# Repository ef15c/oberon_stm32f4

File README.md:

# Oberon STM32F4
Portage of Oberon system to stm32f429i-disco board<br><br>

**Version 15 released!**
## Oberon System
**Improvements:**  

* Divison by zero check is now done by hardware.
* USB Host and Device support added. HID Host and MTP Responder Device are available.
* 16bit integer added to the OM4 compiler (HALFWORD). HALSET and BYTESET types added.
* CLEAR standard procedure is added for setting RECORD and ARRAY variables to zero.
* CPU register protection improved in interrupt handlers.
* Code disassembly tools improved
* The mouse pointer is now managed by hardware. It is no more frozen when system is busy.
* Mira program "chaos esthétique" has been added for testing implementation of REAL type in OM4 compiler.
* Tuning of VESA timings
* Oberon.Batch command has been added for execution of several commands by one mouse click.
* OFS2 replaces the original Project Oberon File System:
  * the sector size is now 2KB instead of 1KB
  * the file size limit is now 12MB instead of 3MB.
  * date and size data are duplicated in the directory entry. Reading the files header sector is no more required in `System.Directory *!` execution.

**Version 14 released!**
## Oberon System
**Improvements:**  

* Edit.ChangeOffset allows formatting indices and exponents in texts  
* Mouse wheel support in text frames
* Scrolling text is now faster
* VGA stability improved
* HOME and END keys supported
* NIL dereferences (trap 4) detection improved
* tests of OM4 compiler with Advent Of Code 2025 puzzles

**Fixes:**

* CapsLock sometimes freezes keyboard fixed
* LED blinking on system panic fixed
* wrong mouse pointer shape in text frames fixed

## MSP430 Oberon compiler
The compiler and linker were rewritten in order to eliminate unused code and data.  
Libraries can now include many procedures and only the ones used in the program
will be placed in the generated firmware.  

A new example including a bootloader and code in RAM feature has been added (bootloader and sDiary).

This toolchain is also available on GNU/Linux amd64 [here](https://github.com/ef15c/omsp).
## Hardware
The base board PCB can be ordered [here](https://www.pcbway.com/project/shareproject/Oberon_STM32F429I_DISCO_station_af64426e.html)  
## Previous releases
A rudimentary image manipulation module is available. It allows to display 8bpp indexed colors BMP and can take screenshots.

**The 12th release contains a major improvement:** the code and strings of the modules can be stored
 in the microcontroller's flash memory and executed in place.
In this case, the global data will be placed is SRAM.  
Previously, the modules had to be loaded into the SDRAM for execution.  
There are a lot of advantages doing this:  

* The code executes 8 times faster, by avoiding the competition between CPU and VGA system for SDRAM access.  
* More SDRAM is available for modules that remain in SDRAM and for the heap.
* If the Oberon system and the compiler are both placed in embedded flash memory,
 the system is guaranteed to boot and compile even if incoherent recompilation has been done on vital modules.
 
 To put modules in embedded flash, follow this procedure:
 
 * Prelink the modules using the command **OM4L.LinkEF**. Example: `OM4L.LinkEF Modules System Edit OM4P ~`  
This will produce a .efb file that will be later placed in the embedded flash memory.
 * Reboot the station in legacy SDRAM mode by pressing the SW1 button on the base board and the reset button on the SMT429I-DISCO board.
  This is mandatory because it is not safe to modify the embedded flash memory while executing it.
 * Install the .efb file using the command **OM4X.LoadEF**. Example: `OM4X.LoadEF OM4P.efb`  
The installation can be verified by comparing the .efb file and the content of the embedded flash,
 using the command **OM4L.CompareEF**. Example: `OM4L.CompareEF OM4P.efb`  
The installation is successful if the output of this command ends with the word "same".
 * Reboot the station without pressing SW1 button. The station should now execute the Oberon system and the compiler from embedded flash.
 This can be checked with the command **System.ShowModules**. In the window that appears,
  all lines refering a module stored in embedded flash will end with the number -1. Example: `OM4P	 0802E7B4 0802F1F4  -1`

Reminder: starting wiht the release 9, it is now easy to launch user actions immediately after system startup.
Put your code in the initialization section of the OnStartup module and compile it.

<br>
QWERTY keyboard can be activated by middle clicking on the text "OM4P.Compile InputQwerty.Mod ~"<br>
displayed in yellow in the middle of the System.Tool window. Restart the system to load the updated Input module.<br>
<br>

<b>Changes in oberon 07 compiler:</b>

<b>Registers usage control in procedures</b><br>
Cortex M4 microcontrollers save automatically a set of registers on stack when servicing an interruption.
If an Oberon exception handler contains too complicated expressions, there is a risk that a non saved register is used.
To prevent that case to happen, I introduced a new notation ^n after the PROCEDURE keyword:<br><br>
PROCEDURE^3 handler;<br>
BEGIN ....<br>
END handler;<br><br>
With this information, the compiler can check  that no more than n registers are used. The save/restoration instructions are automatically generated according to the declared number of used registers.<br>

<b>Unsafe local variables marking</b><br>
This Oberon compiler allow allocation of unitialized pointers on stack.
Those pointers are not checked at runtime, so they are not safe until they are properly intialized.

I made a change in the compiler to allow detection of the declaration of local variables containing pointers.
The developer must check the code to be sure that no bad use is made with these variables.

For example, assume that a Files.Rider is declared as a local variable. Using of the "file" member (eg. via Files.Base) is unsafe until the rider has been initialized with Files.Set.

When the developer has determined that the code usage of the local variable is safe, he or she must mark the variable with an exclamation mark (!) in its declaration.

Oberon runs now on the STM32F429I-DISCO base board:

Hardware side:

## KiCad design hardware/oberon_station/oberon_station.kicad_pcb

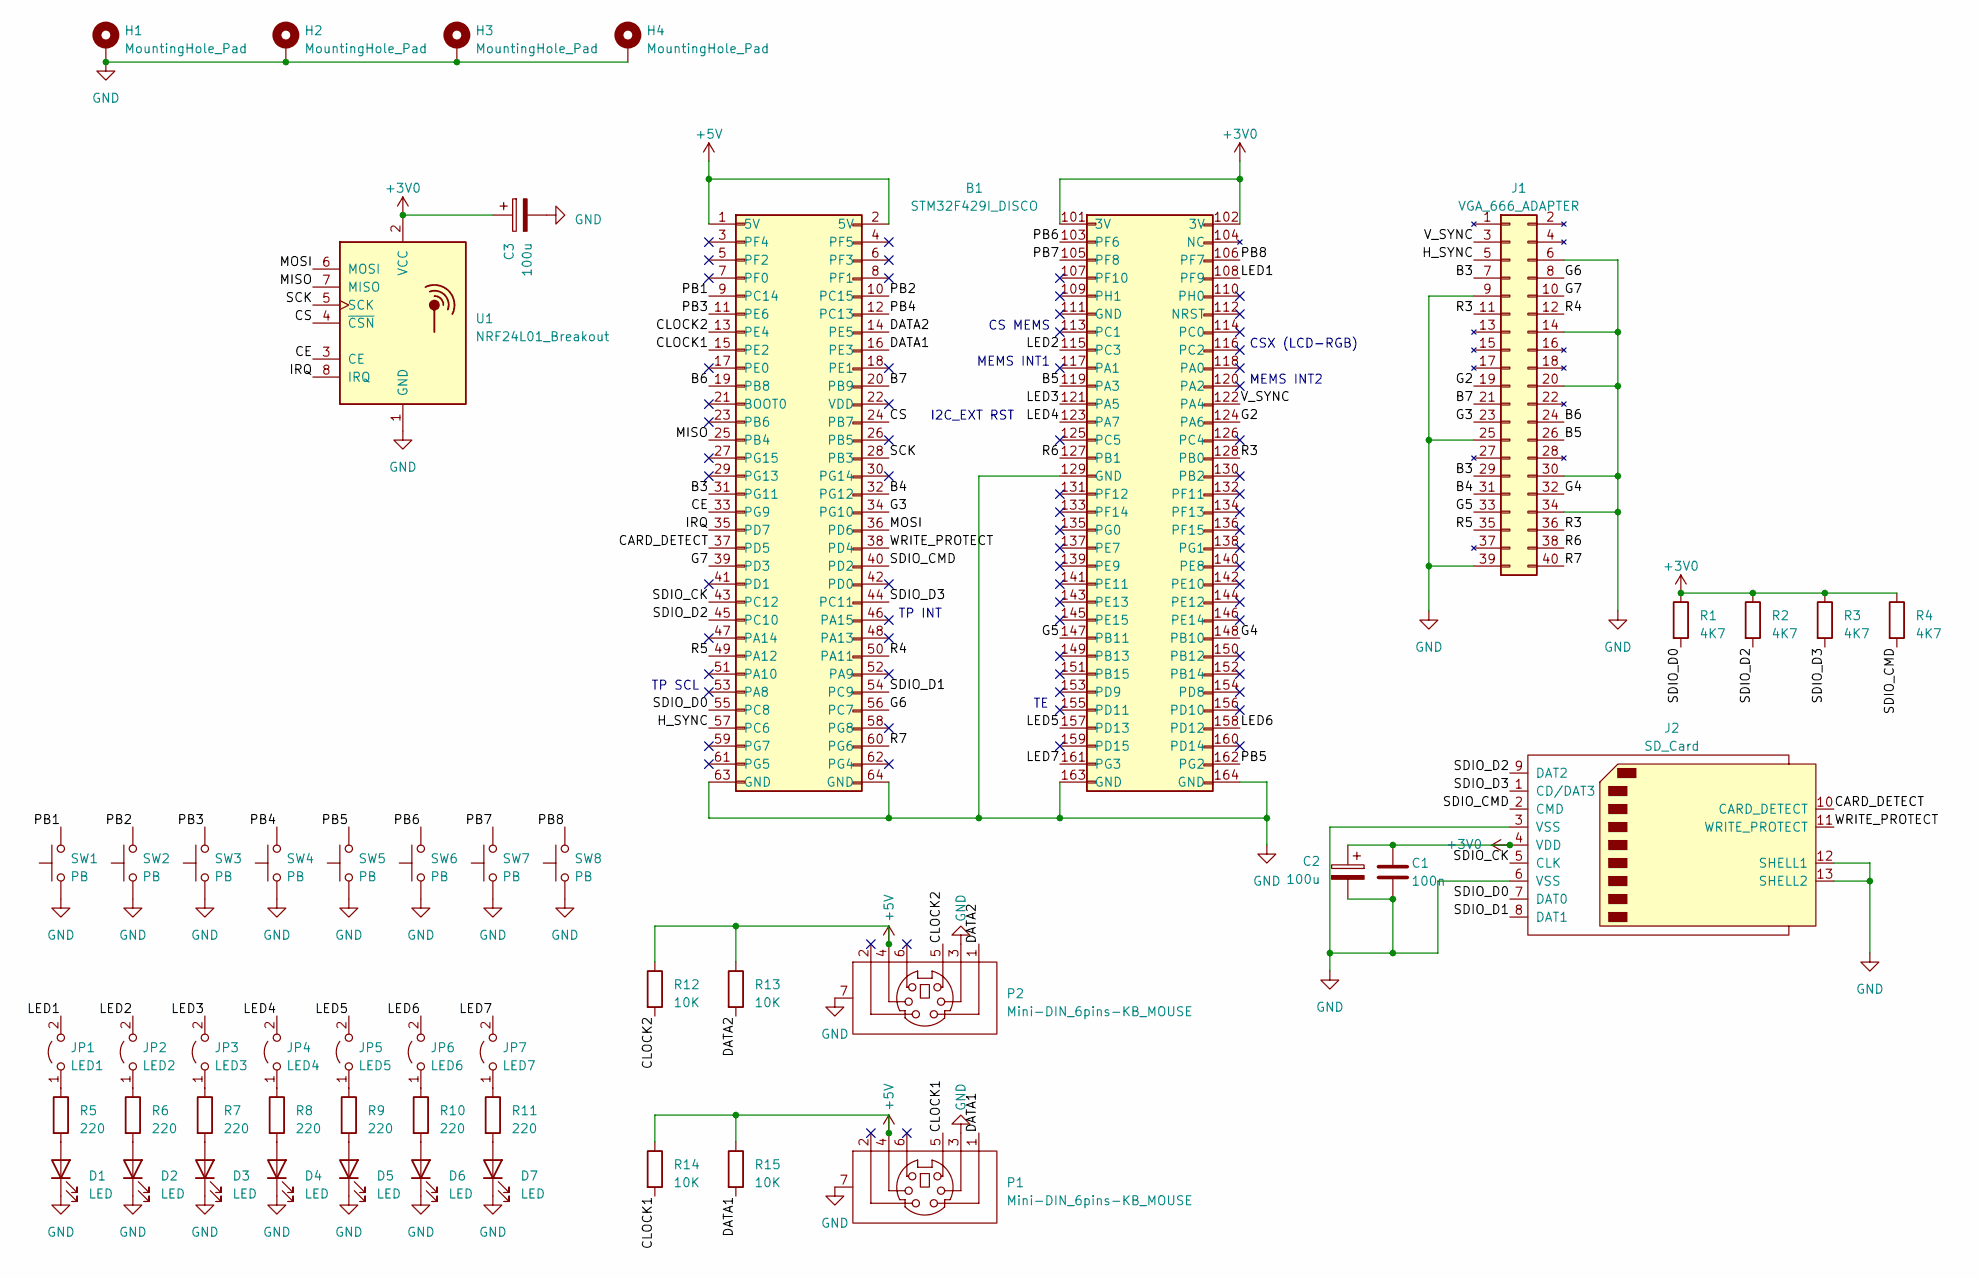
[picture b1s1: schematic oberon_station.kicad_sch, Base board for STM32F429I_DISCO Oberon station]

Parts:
B1: STM32F429I_DISCO
C1: 100n; C_Disc_D7.0mm_W2.5mm_P5.00mm
C2, C3: 100u; CP_Radial_L10.0mm_D4.5mm_Horizontal
D1, D2, D3, D4, D5, D6, D7: LED; LED_D3.0mm
H1, H2, H3, H4: MountingHole_Pad; MountingHole_4.5mm_Pad_Small
J1: VGA_666_ADAPTER; PinHeader_2x20_P2.54mm_Vertical
J2: SD_Card; SD_AC_SL1100
JP1: LED1; TestPoint_2Pads_Pitch2.54mm_Drill0.8mm
JP2: LED2; TestPoint_2Pads_Pitch2.54mm_Drill0.8mm
JP3: LED3; TestPoint_2Pads_Pitch2.54mm_Drill0.8mm
JP4: LED4; TestPoint_2Pads_Pitch2.54mm_Drill0.8mm
JP5: LED5; TestPoint_2Pads_Pitch2.54mm_Drill0.8mm
JP6: LED6; TestPoint_2Pads_Pitch2.54mm_Drill0.8mm
JP7: LED7; TestPoint_2Pads_Pitch2.54mm_Drill0.8mm
P1, P2: Mini-DIN_6pins-KB_MOUSE; Connector_Mini-DIN_Female_6Pin_2rows
R1, R2, R3, R4: 4K7; R_Axial_DIN0207_L6.3mm_D2.5mm_P10.16mm_Horizontal
R5, R6, R7, R8, R9, R10, R11: 220; R_Axial_DIN0207_L6.3mm_D2.5mm_P10.16mm_Horizontal
R12, R13, R14, R15: 10K; R_Axial_DIN0207_L6.3mm_D2.5mm_P10.16mm_Horizontal
SW1, SW2, SW3, SW4, SW5, SW6, SW7, SW8: PB; SW_PUSH_6mm
U1: NRF24L01_Breakout; nRF24L01_Breakout

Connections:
+3V0: B1.101 (3V), B1.102 (3V), C1.1, C2.1, C3.1, J2.4 (VDD), R1.1, R2.1, R3.1, R4.1, U1.2 (VCC)
+5V: B1.1 (5V), B1.2 (5V), P1.4, P2.4, R12.1, R13.1, R14.1, R15.1
/B3: B1.31 (PG11), J1.7 (B2), J1.29 (B3)
/B4: B1.32 (PG12), J1.31 (B4)
/B5: B1.119 (PA3), J1.26 (B5)
/B6: B1.19 (PB8), J1.24 (B6)
/B7: B1.20 (PB9), J1.21 (B7)
/CARD_DETECT: B1.37 (PD5), J2.10 (CARD_DETECT)
/CE: B1.33 (PG9), U1.3 (CE)
/CLOCK1: B1.15 (PE2), P1.5, R14.2
/CLOCK2: B1.13 (PE4), P2.5, R12.2
/CS: B1.24 (PB7), U1.4 (~CSN)
/DATA1: B1.16 (PE3), P1.1, R15.2
/DATA2: B1.14 (PE5), P2.1, R13.2
/G2: B1.124 (PA6), J1.19 (G2)
/G3: B1.34 (PG10), J1.23 (G3)
/G4: B1.148 (PB10), J1.32 (G4)
/G5: B1.147 (PB11), J1.33 (G5)
/G6: B1.56 (PC7), J1.8 (G6)
/G7: B1.39 (PD3), J1.10 (G7)
/H_SYNC: B1.57 (PC6), J1.5 (H_SYNC)
/IRQ: B1.35 (PD7), U1.8 (IRQ)
/LED1: B1.108 (PF9), JP1.2 (B)
/LED2: B1.115 (PC3), JP2.2 (B)
/LED3: B1.121 (PA5), JP3.2 (B)
/LED4: B1.123 (PA7), JP4.2 (B)
/LED5: B1.157 (PD13), JP5.2 (B)
/LED6: B1.158 (PD12), JP6.2 (B)
/LED7: B1.161 (PG3), JP7.2 (B)
/MISO: B1.25 (PB4), U1.7 (MISO)
/MOSI: B1.36 (PD6), U1.6 (MOSI)
/PB1: B1.9 (PC14), SW1.2
/PB2: B1.10 (PC15), SW2.2
/PB3: B1.11 (PE6), SW3.2
/PB4: B1.12 (PC13), SW4.2
/PB5: B1.162 (PG2), SW5.2
/PB6: B1.103 (PF6), SW6.2
/PB7: B1.105 (PF8), SW7.2
/PB8: B1.106 (PF7), SW8.2
/R3: B1.128 (PB0), J1.11 (R3), J1.36 (R2)
/R4: B1.50 (PA11), J1.12 (R4)
/R5: B1.49 (PA12), J1.35 (R5)
/R6: B1.127 (PB1), J1.38 (R6)
/R7: B1.60 (PG6), J1.40 (R7)
/SCK: B1.28 (PB3), U1.5 (SCK)
/SDIO_CK: B1.43 (PC12), J2.5 (CLK)
/SDIO_CMD: B1.40 (PD2), J2.2 (CMD), R4.2
/SDIO_D0: B1.55 (PC8), J2.7 (DAT0), R1.2
/SDIO_D1: B1.54 (PC9), J2.8 (DAT1)
/SDIO_D2: B1.45 (PC10), J2.9 (DAT2), R2.2
/SDIO_D3: B1.44 (PC11), J2.1 (CD/DAT3), R3.2
/V_SYNC: B1.122 (PA4), J1.3 (V_SYNCH)
/WRITE_PROTECT: B1.38 (PD4), J2.11 (WRITE_PROTECT)
GND: B1.63 (GND), B1.64 (GND), B1.129 (GND), B1.163 (GND), B1.164 (GND), C1.2, C2.2, C3.2, D1.1 (K), D2.1 (K), D3.1 (K), D4.1 (K), D5.1 (K), D6.1 (K), D7.1 (K), H1.1, H2.1, H3.1, H4.1, J1.6 (GND), J1.9 (GND), J1.14 (GND), J1.20 (GND), J1.25 (GND), J1.30 (GND), J1.34 (GND), J1.39 (GND), J2.3 (VSS), J2.6 (VSS), J2.12 (SHELL1), J2.13 (SHELL2), P1.3, P1.7 (Shell), P2.3, P2.7 (Shell), SW1.1, SW2.1, SW3.1, SW4.1, SW5.1, SW6.1, SW7.1, SW8.1, U1.1 (GND)
unnamed: D1.2 (A), R5.2
unnamed: D2.2 (A), R6.2
unnamed: D3.2 (A), R7.2
unnamed: D4.2 (A), R8.2
unnamed: D5.2 (A), R9.2
unnamed: D6.2 (A), R10.2
unnamed: D7.2 (A), R11.2
unnamed: JP1.1 (A), R5.1
unnamed: JP2.1 (A), R6.1
unnamed: JP3.1 (A), R7.1
unnamed: JP4.1 (A), R8.1
unnamed: JP5.1 (A), R9.1
unnamed: JP6.1 (A), R10.1
unnamed: JP7.1 (A), R11.1

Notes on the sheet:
MEMS INT1
TP INT
TP SCL
I2C_EXT RST
CSX (LCD-RGB)
CS MEMS
MEMS INT2

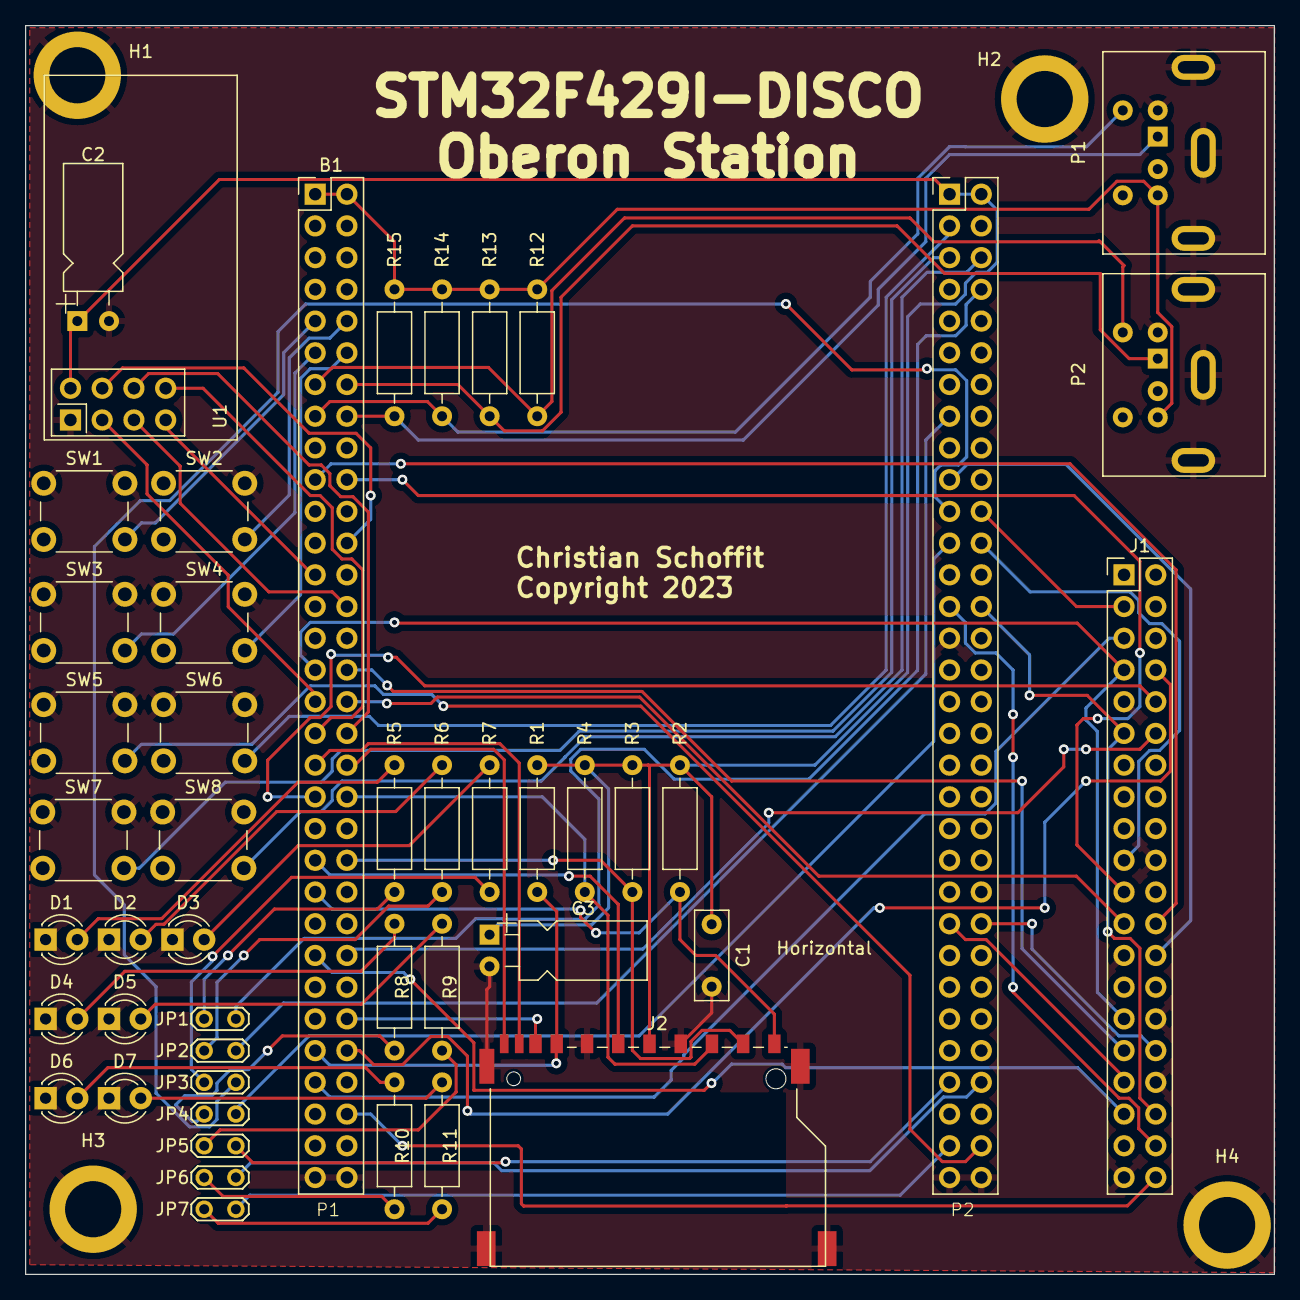
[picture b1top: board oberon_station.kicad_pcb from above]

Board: 4 copper layers, 100.0 x 100.0 mm, 50 parts (0 on the bottom side), 68 nets.

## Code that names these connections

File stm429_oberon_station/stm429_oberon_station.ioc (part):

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Mcu.Name=STM32F429ZITx
Mcu.Package=LQFP144
Mcu.UserName=STM32F429ZITx
PA0/WKUP.GPIOParameters=GPIO_PuPd,GPIO_Label,GPIO_ModeDefaultEXTI
PA0/WKUP.GPIO_Label=B1 [Blue PushButton]
PA0/WKUP.GPIO_ModeDefaultEXTI=GPIO_MODE_EVT_RISING
PA0/WKUP.GPIO_PuPd=GPIO_NOPULL
PA0/WKUP.Signal=GPXTI0
PA10.GPIOParameters=GPIO_Speed,GPIO_Label
PA10.GPIO_Label=STLINK_TX [STM32F103CBT6_PA2]
PA10.GPIO_Speed=GPIO_SPEED_FREQ_LOW
PA10.Mode=Asynchronous
PA10.Signal=USART1_RX
PA11.GPIOParameters=GPIO_Speed,GPIO_PuPd,GPIO_Label,GPIO_Mode
PA11.GPIO_Label=R4
PA11.GPIO_Mode=GPIO_MODE_AF_PP
PA11.GPIO_PuPd=GPIO_NOPULL
PA11.GPIO_Speed=GPIO_SPEED_FREQ_VERY_HIGH
PA11.Mode=RGB565
PA11.Signal=LTDC_R4
PA12.GPIOParameters=GPIO_Speed,GPIO_PuPd,GPIO_Label,GPIO_Mode
PA12.GPIO_Label=R5
PA12.GPIO_Mode=GPIO_MODE_AF_PP
PA12.GPIO_PuPd=GPIO_NOPULL
PA12.GPIO_Speed=GPIO_SPEED_FREQ_VERY_HIGH
PA12.Mode=RGB565
PA12.Signal=LTDC_R5
PA13.GPIOParameters=GPIO_Label
PA13.GPIO_Label=SWDIO
PA13.Mode=Serial_Wire
PA13.Signal=SYS_JTMS-SWDIO
PA14.GPIOParameters=GPIO_Label
PA14.GPIO_Label=SWCLK
PA14.Mode=Serial_Wire
PA14.Signal=SYS_JTCK-SWCLK
PA3.GPIOParameters=GPIO_Speed,GPIO_PuPd,GPIO_Label,GPIO_Mode
PA3.GPIO_Label=B5
PA3.GPIO_Mode=GPIO_MODE_AF_PP
PA3.GPIO_PuPd=GPIO_NOPULL
PA3.GPIO_Speed=GPIO_SPEED_FREQ_VERY_HIGH
PA3.Mode=RGB565
PA3.Signal=LTDC_B5
PA4.GPIOParameters=GPIO_Speed,GPIO_PuPd,GPIO_Label,GPIO_Mode
PA4.GPIO_Label=VSYNC
PA4.GPIO_Mode=GPIO_MODE_AF_PP
PA4.GPIO_PuPd=GPIO_NOPULL
PA4.GPIO_Speed=GPIO_SPEED_FREQ_LOW
PA4.Mode=RGB565
PA4.Signal=LTDC_VSYNC
PA5.GPIOParameters=GPIO_Label
PA5.GPIO_Label=LED3
PA5.Signal=GPIO_Output
PA6.GPIOParameters=GPIO_Speed,GPIO_PuPd,GPIO_Label,GPIO_Mode
PA6.GPIO_Label=G2
PA6.GPIO_Mode=GPIO_MODE_AF_PP
PA6.GPIO_PuPd=GPIO_NOPULL
PA6.GPIO_Speed=GPIO_SPEED_FREQ_VERY_HIGH
PA6.Mode=RGB565
PA6.Signal=LTDC_G2
PA7.GPIOParameters=GPIO_Label
PA7.GPIO_Label=LED4
PA7.Signal=GPIO_Output
PA9.GPIOParameters=GPIO_Speed,GPIO_Label
PA9.GPIO_Label=STLINK_RX [STM32F103CBT6_PA3]
PA9.GPIO_Speed=GPIO_SPEED_FREQ_LOW
PA9.Mode=Asynchronous
PA9.Signal=USART1_TX
PB0.GPIOParameters=GPIO_Speed,GPIO_PuPd,GPIO_Label,GPIO_Mode
PB0.GPIO_Label=R3
PB0.GPIO_Mode=GPIO_MODE_AF_PP
PB0.GPIO_PuPd=GPIO_NOPULL
PB0.GPIO_Speed=GPIO_SPEED_FREQ_VERY_HIGH
PB0.Mode=RGB565
PB0.Signal=LTDC_R3
PB1.GPIOParameters=GPIO_Speed,GPIO_PuPd,GPIO_Label,GPIO_Mode
PB1.GPIO_Label=R6
PB1.GPIO_Mode=GPIO_MODE_AF_PP
PB1.GPIO_PuPd=GPIO_NOPULL
PB1.GPIO_Speed=GPIO_SPEED_FREQ_VERY_HIGH
PB1.Mode=RGB565
PB1.Signal=LTDC_R6
PB10.GPIOParameters=GPIO_Speed,GPIO_PuPd,GPIO_Label,GPIO_Mode
PB10.GPIO_Label=G4
PB10.GPIO_Mode=GPIO_MODE_AF_PP
PB10.GPIO_PuPd=GPIO_NOPULL
PB10.GPIO_Speed=GPIO_SPEED_FREQ_VERY_HIGH
PB10.Mode=RGB565
PB10.Signal=LTDC_G4
PB11.GPIOParameters=GPIO_Speed,GPIO_PuPd,GPIO_Label,GPIO_Mode
PB11.GPIO_Label=G5
PB11.GPIO_Mode=GPIO_MODE_AF_PP
PB11.GPIO_PuPd=GPIO_NOPULL
PB11.GPIO_Speed=GPIO_SPEED_FREQ_VERY_HIGH
PB11.Mode=RGB565
PB11.Signal=LTDC_G5
PB2/BOOT1.GPIOParameters=GPIO_PuPd,GPIO_Label,GPIO_Mode
PB2/BOOT1.GPIO_Label=BOOT1
PB2/BOOT1.GPIO_Mode=GPIO_MODE_INPUT
PB2/BOOT1.GPIO_PuPd=GPIO_NOPULL
PB2/BOOT1.Signal=GPIO_Input
PB3.GPIOParameters=GPIO_Speed,GPIO_Label
PB3.GPIO_Label=NRF24L01P_SCK
PB3.GPIO_Speed=GPIO_SPEED_FREQ_MEDIUM
PB3.Mode=Full_Duplex_Master
PB3.Signal=SPI3_SCK
PB4.GPIOParameters=GPIO_Speed,GPIO_Label
PB4.GPIO_Label=NRF24L01P_MISO
PB4.GPIO_Speed=GPIO_SPEED_FREQ_MEDIUM
PB4.Mode=Full_Duplex_Master
PB4.Signal=SPI3_MISO
PB5.GPIOParameters=GPIO_Speed,GPIO_PuPd,GPIO_Label,GPIO_Mode
PB5.GPIO_Label=SDCKE1
PB5.GPIO_Mode=GPIO_MODE_AF_PP
PB5.GPIO_PuPd=GPIO_NOPULL
PB5.GPIO_Speed=GPIO_SPEED_FREQ_VERY_HIGH
PB5.Mode=SdramChipSelect2_1
PB5.Signal=FMC_SDCKE1
PB6.GPIOParameters=GPIO_Speed,GPIO_PuPd,GPIO_Label,GPIO_Mode
PB6.GPIO_Label=SDNE1 [SDRAM_CS]
PB6.GPIO_Mode=GPIO_MODE_AF_PP
PB6.GPIO_PuPd=GPIO_NOPULL
PB6.GPIO_Speed=GPIO_SPEED_FREQ_VERY_HIGH
PB6.Mode=SdramChipSelect2_1
PB6.Signal=FMC_SDNE1
PB7.GPIOParameters=GPIO_Speed,PinState,GPIO_Label
PB7.GPIO_Label=NRF24L01P_CS
PB7.GPIO_Speed=GPIO_SPEED_FREQ_LOW
PB7.PinState=GPIO_PIN_SET
PB7.Signal=GPIO_Output
PB8.GPIOParameters=GPIO_Speed,GPIO_PuPd,GPIO_Label,GPIO_Mode
PB8.GPIO_Label=B6
PB8.GPIO_Mode=GPIO_MODE_AF_PP
PB8.GPIO_PuPd=GPIO_NOPULL
PB8.GPIO_Speed=GPIO_SPEED_FREQ_VERY_HIGH
PB8.Mode=RGB565
PB8.Signal=LTDC_B6
PB9.GPIOParameters=GPIO_Speed,GPIO_PuPd,GPIO_Label,GPIO_Mode
PB9.GPIO_Label=B7
PB9.GPIO_Mode=GPIO_MODE_AF_PP
PB9.GPIO_PuPd=GPIO_NOPULL
PB9.GPIO_Speed=GPIO_SPEED_FREQ_VERY_HIGH
PB9.Mode=RGB565
PB9.Signal=LTDC_B7
PC0.GPIOParameters=GPIO_Speed,GPIO_PuPd,GPIO_Label,GPIO_Mode
PC0.GPIO_Label=SDNWE
PC0.GPIO_Mode=GPIO_MODE_AF_PP
PC0.GPIO_PuPd=GPIO_NOPULL
PC0.GPIO_Speed=GPIO_SPEED_FREQ_VERY_HIGH
PC0.Signal=FMC_SDNWE
PC1.GPIOParameters=GPIO_Speed,PinState,GPIO_PuPd,GPIO_Label,GPIO_Mode
PC1.GPIO_Label=NCS_MEMS_SPI [L3GD20_CS_I2C/SPI]
PC1.GPIO_Mode=GPIO_MODE_OUTPUT_PP
PC1.GPIO_PuPd=GPIO_NOPULL
PC1.GPIO_Speed=GPIO_SPEED_FREQ_LOW
PC1.PinState=GPIO_PIN_SET
PC1.Signal=GPIO_Output
PC10.GPIOParameters=GPIO_Speed_High_Default
PC10.GPIO_Speed_High_Default=GPIO_SPEED_FREQ_HIGH
PC10.Mode=SD_4_bits_Wide_bus
PC10.Signal=SDIO_D2
PC11.GPIOParameters=GPIO_Speed_High_Default
PC11.GPIO_Speed_High_Default=GPIO_SPEED_FREQ_HIGH
PC11.Mode=SD_4_bits_Wide_bus
PC11.Signal=SDIO_D3
PC12.GPIOParameters=GPIO_Speed_High_Default
PC12.GPIO_Speed_High_Default=GPIO_SPEED_FREQ_HIGH
PC12.Mode=SD_4_bits_Wide_bus
PC12.Signal=SDIO_CK
PC13.GPIOParameters=GPIO_PuPd,GPIO_Label
PC13.GPIO_Label=PB4
PC13.GPIO_PuPd=GPIO_PULLUP
PC13.Signal=GPIO_Input
PC14/OSC32_IN.GPIOParameters=GPIO_PuPd,GPIO_Label,GPIO_ModeDefaultEXTI
PC14/OSC32_IN.GPIO_Label=PB1
PC14/OSC32_IN.GPIO_ModeDefaultEXTI=GPIO_MODE_IT_FALLING
PC14/OSC32_IN.GPIO_PuPd=GPIO_PULLUP
PC14/OSC32_IN.Signal=GPXTI14
PC15/OSC32_OUT.GPIOParameters=GPIO_PuPd,GPIO_Label
PC15/OSC32_OUT.GPIO_Label=PB2
PC15/OSC32_OUT.GPIO_PuPd=GPIO_PULLUP
PC15/OSC32_OUT.Signal=GPIO_Input
PC2.GPIOParameters=GPIO_Speed,PinState,GPIO_PuPd,GPIO_Label,GPIO_Mode
PC2.GPIO_Label=CSX [LCD-RGB_CSX]
PC2.GPIO_Mode=GPIO_MODE_OUTPUT_PP
PC2.GPIO_PuPd=GPIO_NOPULL
PC2.GPIO_Speed=GPIO_SPEED_FREQ_LOW
PC2.PinState=GPIO_PIN_SET
PC2.Signal=GPIO_Output
PC3.GPIOParameters=GPIO_Label
PC3.GPIO_Label=LED2
PC3.Signal=GPIO_Output
PC6.GPIOParameters=GPIO_Speed,GPIO_PuPd,GPIO_Label,GPIO_Mode
PC6.GPIO_Label=HSYNC
PC6.GPIO_Mode=GPIO_MODE_AF_PP
PC6.GPIO_PuPd=GPIO_NOPULL
PC6.GPIO_Speed=GPIO_SPEED_FREQ_VERY_HIGH
PC6.Mode=RGB565
PC6.Signal=LTDC_HSYNC
PC7.GPIOParameters=GPIO_Speed,GPIO_PuPd,GPIO_Label,GPIO_Mode
PC7.GPIO_Label=G6
PC7.GPIO_Mode=GPIO_MODE_AF_PP
PC7.GPIO_PuPd=GPIO_NOPULL
PC7.GPIO_Speed=GPIO_SPEED_FREQ_VERY_HIGH
PC7.Mode=RGB565
PC7.Signal=LTDC_G6
PC8.GPIOParameters=GPIO_Speed_High_Default
PC8.GPIO_Speed_High_Default=GPIO_SPEED_FREQ_HIGH
PC8.Mode=SD_4_bits_Wide_bus
PC8.Signal=SDIO_D0
PC9.GPIOParameters=GPIO_Speed_High_Default
PC9.GPIO_Speed_High_Default=GPIO_SPEED_FREQ_HIGH
PC9.Mode=SD_4_bits_Wide_bus
PC9.Signal=SDIO_D1
PD0.GPIOParameters=GPIO_Speed,GPIO_PuPd,GPIO_Label,GPIO_Mode
PD0.GPIO_Label=D2
PD0.GPIO_Mode=GPIO_MODE_AF_PP
PD0.GPIO_PuPd=GPIO_NOPULL
PD0.GPIO_Speed=GPIO_SPEED_FREQ_VERY_HIGH
PD0.Signal=FMC_D2_DA2
PD1.GPIOParameters=GPIO_Speed,GPIO_PuPd,GPIO_Label,GPIO_Mode
PD1.GPIO_Label=D3
PD1.GPIO_Mode=GPIO_MODE_AF_PP
PD1.GPIO_PuPd=GPIO_NOPULL
PD1.GPIO_Speed=GPIO_SPEED_FREQ_VERY_HIGH
PD1.Signal=FMC_D3_DA3
PD10.GPIOParameters=GPIO_Speed,GPIO_PuPd,GPIO_Label,GPIO_Mode
PD10.GPIO_Label=D15
PD10.GPIO_Mode=GPIO_MODE_AF_PP
PD10.GPIO_PuPd=GPIO_NOPULL
PD10.GPIO_Speed=GPIO_SPEED_FREQ_VERY_HIGH
PD10.Signal=FMC_D15_DA15
PD12.GPIOParameters=GPIO_Label
PD12.GPIO_Label=LED6
PD12.Signal=GPIO_Output
PD13.GPIOParameters=GPIO_Label
PD13.GPIO_Label=LED5
PD13.Signal=GPIO_Output
PD14.GPIOParameters=GPIO_Speed,GPIO_PuPd,GPIO_Label,GPIO_Mode
PD14.GPIO_Label=D0
PD14.GPIO_Mode=GPIO_MODE_AF_PP
PD14.GPIO_PuPd=GPIO_NOPULL
PD14.GPIO_Speed=GPIO_SPEED_FREQ_VERY_HIGH
PD14.Signal=FMC_D0_DA0
PD15.GPIOParameters=GPIO_Speed,GPIO_PuPd,GPIO_Label,GPIO_Mode
PD15.GPIO_Label=D1
PD15.GPIO_Mode=GPIO_MODE_AF_PP
PD15.GPIO_PuPd=GPIO_NOPULL
PD15.GPIO_Speed=GPIO_SPEED_FREQ_VERY_HIGH
PD15.Signal=FMC_D1_DA1
PD2.GPIOParameters=GPIO_Speed_High_Default
PD2.GPIO_Speed_High_Default=GPIO_SPEED_FREQ_HIGH
PD2.Mode=SD_4_bits_Wide_bus
PD2.Signal=SDIO_CMD
PD3.GPIOParameters=GPIO_Speed,GPIO_PuPd,GPIO_Label,GPIO_Mode
PD3.GPIO_Label=G7
PD3.GPIO_Mode=GPIO_MODE_AF_PP
PD3.GPIO_PuPd=GPIO_NOPULL
PD3.GPIO_Speed=GPIO_SPEED_FREQ_VERY_HIGH
PD3.Mode=RGB565
PD3.Signal=LTDC_G7
PD4.GPIOParameters=GPIO_PuPd,GPIO_Label
PD4.GPIO_Label=WRITE_PROTECT
PD4.GPIO_PuPd=GPIO_PULLUP
PD4.Signal=GPIO_Input
PD5.GPIOParameters=GPIO_PuPd,GPIO_Label
PD5.GPIO_Label=CARD_DETECT
PD5.GPIO_PuPd=GPIO_PULLUP
PD5.Signal=GPIO_Input
PD6.GPIOParameters=GPIO_Speed,GPIO_Label
PD6.GPIO_Label=NRF24L01P_MOSI
PD6.GPIO_Speed=GPIO_SPEED_FREQ_MEDIUM
PD6.Mode=Full_Duplex_Master
PD6.Signal=SPI3_MOSI
PD7.GPIOParameters=GPIO_Label
PD7.GPIO_Label=NRF24L01P_IRQ
PD7.Signal=GPIO_Input
PD8.GPIOParameters=GPIO_Speed,GPIO_PuPd,GPIO_Label,GPIO_Mode
PD8.GPIO_Label=D13
PD8.GPIO_Mode=GPIO_MODE_AF_PP
PD8.GPIO_PuPd=GPIO_NOPULL
PD8.GPIO_Speed=GPIO_SPEED_FREQ_VERY_HIGH

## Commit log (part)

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2025-01-05 Amélioration OM4D et ajout System.CompareFiles
2025-01-06 Amélioration OM4D
2025-01-07 Version intermédiaire du support des entiers sur 64 bits
2025-01-08 Amélioration System.Free et nettoyage code OMSP
    System.Free désalloue maintenant la mémoire utilisée par les modules
    situés à la fin de la zone de stockage des modules.
    Suppression de l'allocation dynamique dans OMSPTool.
2025-01-08 Correction OMSP et OM4 64bit integers
2025-01-08 Correction OM4 64bit integers
2025-01-11 Ajout support des entiers 64bits dans OM4
2025-01-11 Amélioration OM4D, correction OM4G2
2025-01-12 correction OM4G2
2025-01-14 Amélioration OM4D, OM4A2 et OM4G2
2025-01-15 Corrections OM4A et OM4x2, création LongDiv
2025-01-16 Amélioration OM4D, corrections OM4x2
2025-01-21 Correction OM4x2 et OMSPP, module de hachage
2025-01-22 Correction du module de hachage, ajout d'un module de traçage et d'un test basé sur le problème AOC2024 jour 11
2025-01-22 Correction du module de hachage
2025-01-24 Correction OM4G2 et OM4P2
2025-01-24 Amélioration OM4A2x et ajout d'un test basé sur le problème AOC2024 jour 13
2025-01-24 Amélioration OM4G2
2025-01-26 Ajout d'un programme de test basé sur AOC2024 day 19
2025-01-27 Amélioration UTHash
2025-01-30 Correction OM4A et OM4x2
    Ajout d'une exemple de test basé sur AOC 2024 Day 20
2025-02-01 Correction TextFrames, optimisation OM4G2.Mod
    Amélioration UTHash et ajout d'un exemple basé sur AOC 2024 day 21
2025-02-02 Correction FontUtils et ajout de la police Mono10.Scn.Fnt
2025-02-04 Amélioration UTHash
    Ajout d'un test basé sur AOC 2024 Day 22
2025-02-05 Stabilisation OM4x2
2025-02-06 Optimisation du code généré par OM4 et correction OM4P
2025-02-09 Nettoyage du code, corrections OMSPx et Texts
2025-02-15 Clean code and fix minor bugs in OMSPx
2025-02-19 Correction du test "31 IN set"
2025-02-19 Optimisation de l'utilisation mémmoire des modules
2025-02-19 Correction documenatatin omsp
2025-02-19 Mise à jour FLASH et documentation omsp
2025-02-19 Mise à jour documenttion omsp
2025-02-21 Mise au point du module FLASH
2025-02-21 Correction d'une regression entraînant une boucle infinie dans Modules
    et correction d'une erreur d'affichage dans OM4X
2025-02-21 Correction de la documentation omsp
2025-02-23 Correction BSP
2025-02-24 Ajout OM4X.Load
    Permet le flashage "in situ" du code d'amorçage (OM4X.Load BootLoad.hex)
2025-02-25 Amélioration OM4L
    Ajout d'une section de code qui appelle les blocs d'initialisation de
    chaque module lié.
2025-03-01 Préparation au stockage des modules en mémoire flash embarquée
    - Réécriture de l'initialisation de smodules du niveau "inner"
    - Mise en place de segments flash, sram et sdram dans OM4L
    - Ajout du champ "const" dans Modules.Module
    - Affichage du champ "const" dans OM4Tool
2025-03-04 Suite préparation au stockage des modules en mémoire flash embarquée
    et correction OM4D
2025-03-05 Suite préparation au stockage des modules en mémoire flash embarquée
2025-03-07 Ajout d'un suivi de l'utilisation de la pile principale
2025-03-08 Amélioration OM4x
    Ajout d'une procedure standard SYSTEM.JUMP pour égérer un saut vers une
    adresse 32 bits connue à la compilation
2025-03-09 Paramétrisation de la position des paramètres de boot
2025-03-09 SUpression de la mise à jour au démarrage des paramètre de boot
2025-03-09 Ajout de la procedure de création de binaire embarqué
2025-03-10 Amélioration OM4D et correction OM4L.LinkEF
2025-03-13 Modification BootLoad pour stockage des modules en mémoire flash embarquée
    Corrections BSP, Modules, OM4L
2025-03-14 Mise en place des modules de base dans la mémoire flash embarquée
2025-03-14 Boote par défaut avec les modules en mémoire flash embarquée
    Correction Modules
2025-03-14 Correction Modules
2025-03-14 Vérification de la présence des modules en flash
2025-03-15 Corections OM4x et adaptation du système Oberon à un hébergement en Flash
2025-03-17 Correction OM4x RECORD non exportés
    Mise à jour de BuildM4.Tool pour prendre en compte l'exécution des
    modules à partir de la mémoire flash.
2025-03-17 Refonte de l'initialisation des modules résidents
2025-03-17 Test de performance des modules résident
2025-03-21 Ajustement des fichies .Tool
2025-03-21 Toilettages des modules AOC 2024
2025-03-21 Augmentation du délai dans SetCapsLock
2025-03-24 Finalisation de l'exemple MSP430G2231
2025-03-30 Amélioration OM4G, correction PS2
2025-03-30 Ajout du support de constantes stockées dans OMSP
2025-04-01 Optimisation OMSP
2025-04-01 Amélioration et correction OM4
2025-04-02 Suite de l'ajout du support de constantes stockées dans OMSP
2025-04-05 Amélioration de Tools
2025-04-10 Ajout de la procédure standard PTR et correction OMSP
2025-04-11 Anticipation de l'initialisation VGA
2025-04-11 Transformation de la procédure standard PTR en fonction standard
2025-04-12 Correction OMSP
2025-04-12 Ajout d'un programme MSP430G2553 Relay COTA
2025-04-14 Correction nrf24l01p relay COTA
2025-04-15 Correction testPS2
2025-04-16 Amélioration Net
2025-04-16 Amélioration OMSPG
2025-04-16 Optimisation du code
2025-04-18 Amélioration OM4L
2025-04-18 Correction OMSPG
2025-04-18 Préparation de la release 12
2025-04-18 Correction README.md
2025-04-18 Mise à jour README.md
2025-04-18 Correction de la documentation
2025-04-25 Création d'un programme d'affichage d'images BMP
2025-04-25 Recompilation de programmes MSP430
2025-04-25 Modification de Display.Dot pour l'affichage des couleurs
2025-04-25 Correction d'un programme d'affichage d'images BMP
2025-04-26 Ajout de la commande Image.ScreenShot
2025-05-10 Préparation de la release 13
2025-05-30 Amélioration récupération sur erreur
2025-06-10 Amélioration OMSP
2025-06-10 Amélioration brownout
2025-06-10 Ajout d'un exemple msp430g2553: bootloader
2025-06-10 Amélioration du code bootloader
2025-08-24 Ajout fonctionnalité Edit.ChangeOffset
2025-09-09 Fiablilisation du bootloader
    Utilisation d'une adresse par défaut en dehors de l'espace d'adressage
    de la méomire flash.
2025-09-16 Optimisation du code généré par OMSPG
2025-09-18 Ajout de la procédure standard NEG
2025-09-19 Correction d'un bug dans OMSPG - amélioration MP artihmétique
2025-09-19 Correction d'un bug dans OMSPG
2025-09-21 Amélioration OMSPG et MultiPrecisionArith
2025-09-23 Support des souris à roulette
2025-09-30 Optimisation TextFrames scroll down
2025-09-30 Amélioration du défilement avec la molette de souris
2025-10-01 Correction OMSPP
2025-10-04 Déplacement nrf24l01p et pcd8544
2025-10-04 Amélioration bootloader
2025-10-08 Correction comportement roulette quand un TRAP survient
2025-10-08 Amélioration de la généricité de pcd8544
2025-10-08 Actualisation de System.Tool
2025-10-08 Déport de la convertion entier en chaine
2025-10-08 Amélioration affichage des messages et marqueur star
    Image.Mod : prise en compte du marqueur star
    OM4L et OM4P : délai d'affichage des messages d'initialisation
2025-10-12 Amélioration OMSP
    Détection des objets non référencés
    Amélioration de la copie de structures
2025-10-12 Amélioration pcd8544
2025-10-12 Amélioration unroll StoreStruct OMSPG
2025-10-13 Corrections OMSPB et OMSPP, améliorations OMSPS
2025-10-14 Optimisation OM4 - Correction Kernel.Mod
    Détection matérielle du déréférencement d'un pointeur nul (Trap 4).
    Cela permet la suppression du code de test généré par Om4G.NilCheck.
    Correction Kernel.defaultHandler
2025-10-19 Création d'un module DMA pour accélérer les copies mémoire
2025-10-19 Correction OMSPB
2025-10-21 Amélioration OMSP, correction PosixTime
2025-11-11 Correction d'un blocage clavier sur CapsLock
2025-11-11 Amélioration testRS232
2025-11-11 Exports complémentaires du module pcd8544
2025-11-12 Correction TextFrames
2025-11-15 Correction initialisation PS/2
2025-11-16 Ajout du support des touches clavier HOME et END
2025-11-20 Refonte OMSP - utilisation de sections de code pour pouvoir ensuite supprimer le code ou les données non référencées de l'exécutable final - simplification du code de génération des instruction MSP430
2025-11-20 Test du nouveau format objet
2025-11-21 Amélioration de la détection de déréferencement de pointeur NIL
2025-11-21 Corrections OMSP
2025-11-23 Correction OMPS
2025-12-01 Advent Of Code 2025 Day 1
2025-12-02 Fusion du contenu de TextsEx dans Texts
2025-12-02 Advant Of Code 2025 Day 2
2025-12-03 Advent Of Code 2025 Day 2
2025-12-03 Corrections OMSPG
2025-12-05 Amélioration OMSPL
2025-12-05 Adevent of Code days 4 and 5
2025-12-06 Advent of Code day 6
2025-12-07 Correction OM4 LONGINT
2025-12-07 Advent of Code 2025 day 7
2025-12-07 Déplacement de procédures de FilesEx vers Files
2025-12-08 Advent of Code 2025 day 8
2025-12-09 Advent of Code 2025 day 9
2025-12-10 Advent of Code day 10 part one
2025-12-15 Advent of Code day 11
2025-12-15 Correction OM4P
2025-12-16 Amélioration des messages d'erreur System.Free
2025-12-16 Correction de la fonction standard ABS appliquée au type LONGINT
2025-12-17 Corrections calcul sur rationnels
2025-12-27 Advent of Code day 10 part
2026-01-01 Elimination des sections de code non référencé
2026-01-02 Déboguage OMSP
2026-01-13 Correction MultiPrecisionArith
2026-01-13 Correction sDiary
2026-01-14 Corrections PosixTime
2026-01-16 Corrections sDiary
2026-01-19 Préparation de la release 14
2026-01-19 Correction readme
2026-02-02 Améliorations OMSP
2026-03-04 Détection matérielle de divison par zéro
2026-03-29 Préparation du support d'hôte USB
2026-03-29 Advent of Code 2017 Day 10
2026-03-29 Correction du module PosixTime
2026-04-09 Support des entiers 16 bits sans signe (HALFWORD)
2026-04-15 Amélioration de la protection des registres dans le traitment des interruptions
2026-04-17 Amélioration de la protection des registres
    Utilisation de la LED 6 pour indiquer la charge du système
2026-04-18 Amélioration de la protection des registres
2026-04-25 Utilisation de DMA dans Display.ReplConst
2026-05-04 Architecture des modules USB Host
2026-05-05 Correction bogue chaines exportées
2026-05-07 Ajout des types BYTESET et HALFSET
2026-05-10 Déplacement de la marque de texte modifié
2026-05-12 Amélioration Kernel.Mark, BSP.InitDisplay, TextFrames
    Suppression d'un possible TRAP 8 dans Kernel.Mark
    Repositionnement de la marque de texte modifié
2026-05-19 Ajout LTDC Layer 2 dans BSP.Mod
2026-05-19 Gestion du curseur de souris par LTDC L2
2026-05-19 Test LTDC
2026-05-19 Correction régression SETSTAR
2026-05-20 Correction d'une régression dans le module TextFrames
2026-05-20 Adaptation à la nouvelle gestion du pointeur de souris
2026-05-25 Amélioration pointeur busy
2026-05-25 Support USB hôte
    Portage de la bilbiothèque STM usb_host
2026-05-25 Corrections pile USB
2026-06-02 Amélioration de la pile USB
    Suppression des transtypages dangereux,
    simplification du décodage des descripteurs
2026-06-02 Ajout de la procedure standard CLEAR
2026-06-02 Correction de l'affichage des pointeurs de souris
2026-06-02 Mise à jour de la configuration matérielle
2026-06-02 Désassemblage des modules logés en mémoire flash
2026-06-03 Correction et nettoyage code pile USB
2026-06-06 Traitement différé de certaines interruptions de la pile USB
2026-06-06 Mise à jour du tableau des dépendences
2026-06-07 Amélioration de la pile USB
2026-06-12 Correction marque de texte modifié
    et déplacement du fichier Draw.Tool
    nettoyage de code
2026-06-12 Suppression d'un fichier obsolète
2026-06-12 Correction du module Display
2026-06-17 Corrections et améliorations
    - correctopn marque de texte modifié et CopyPattern
    - amélioration de l'affichage des menus textes
2026-06-18 Suite de la pile USB
2026-06-21 Corrections de la pile USB
2026-06-22 Corrections et améliorations de la pile USB
2026-06-24 Corrections de la pile USB et module System
2026-06-25 Amélioration Kernel et System
2026-06-25 Correction de la pile USB: le clavier fonctionne
2026-06-26 Corrections de la pile USB: la souris fonctionne
2026-06-26 Correction du langage incorractement classifié en Modula2
    Correction d'une erreur de frappe dans notes.txt
2026-06-26 Correction d'une erreur de frappe dans notes.txt

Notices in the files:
hardware/oberon_station/oberon_station.kicad_pcb:
Copyright 2023
